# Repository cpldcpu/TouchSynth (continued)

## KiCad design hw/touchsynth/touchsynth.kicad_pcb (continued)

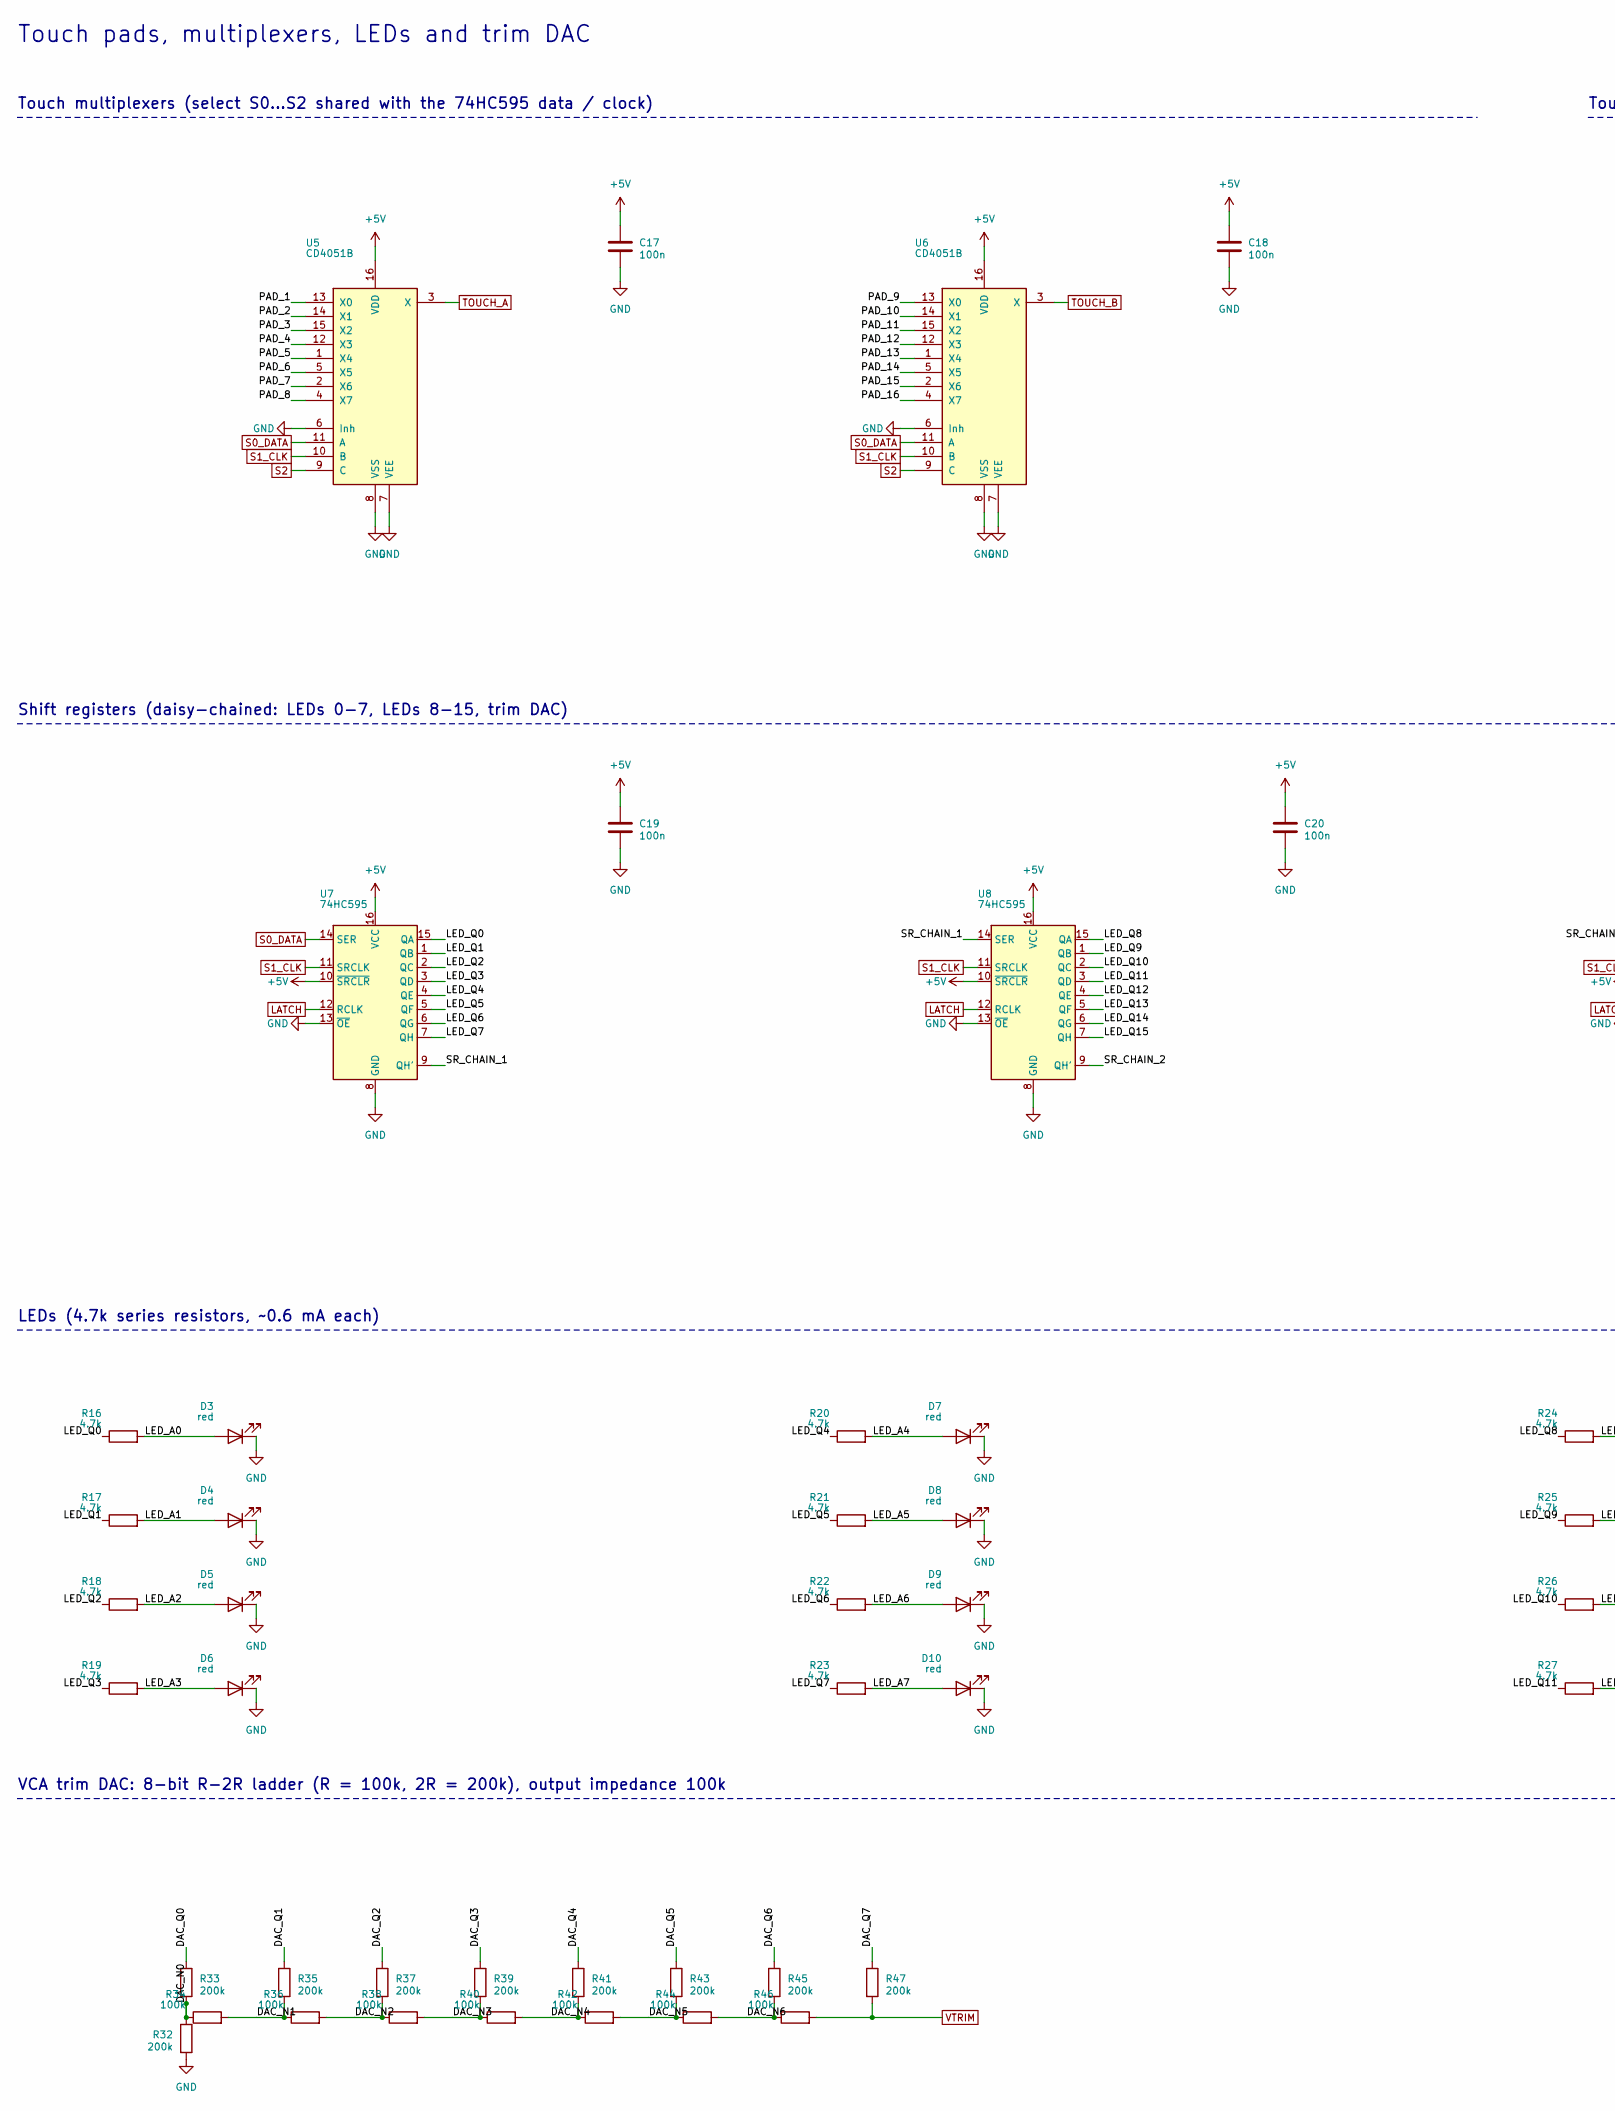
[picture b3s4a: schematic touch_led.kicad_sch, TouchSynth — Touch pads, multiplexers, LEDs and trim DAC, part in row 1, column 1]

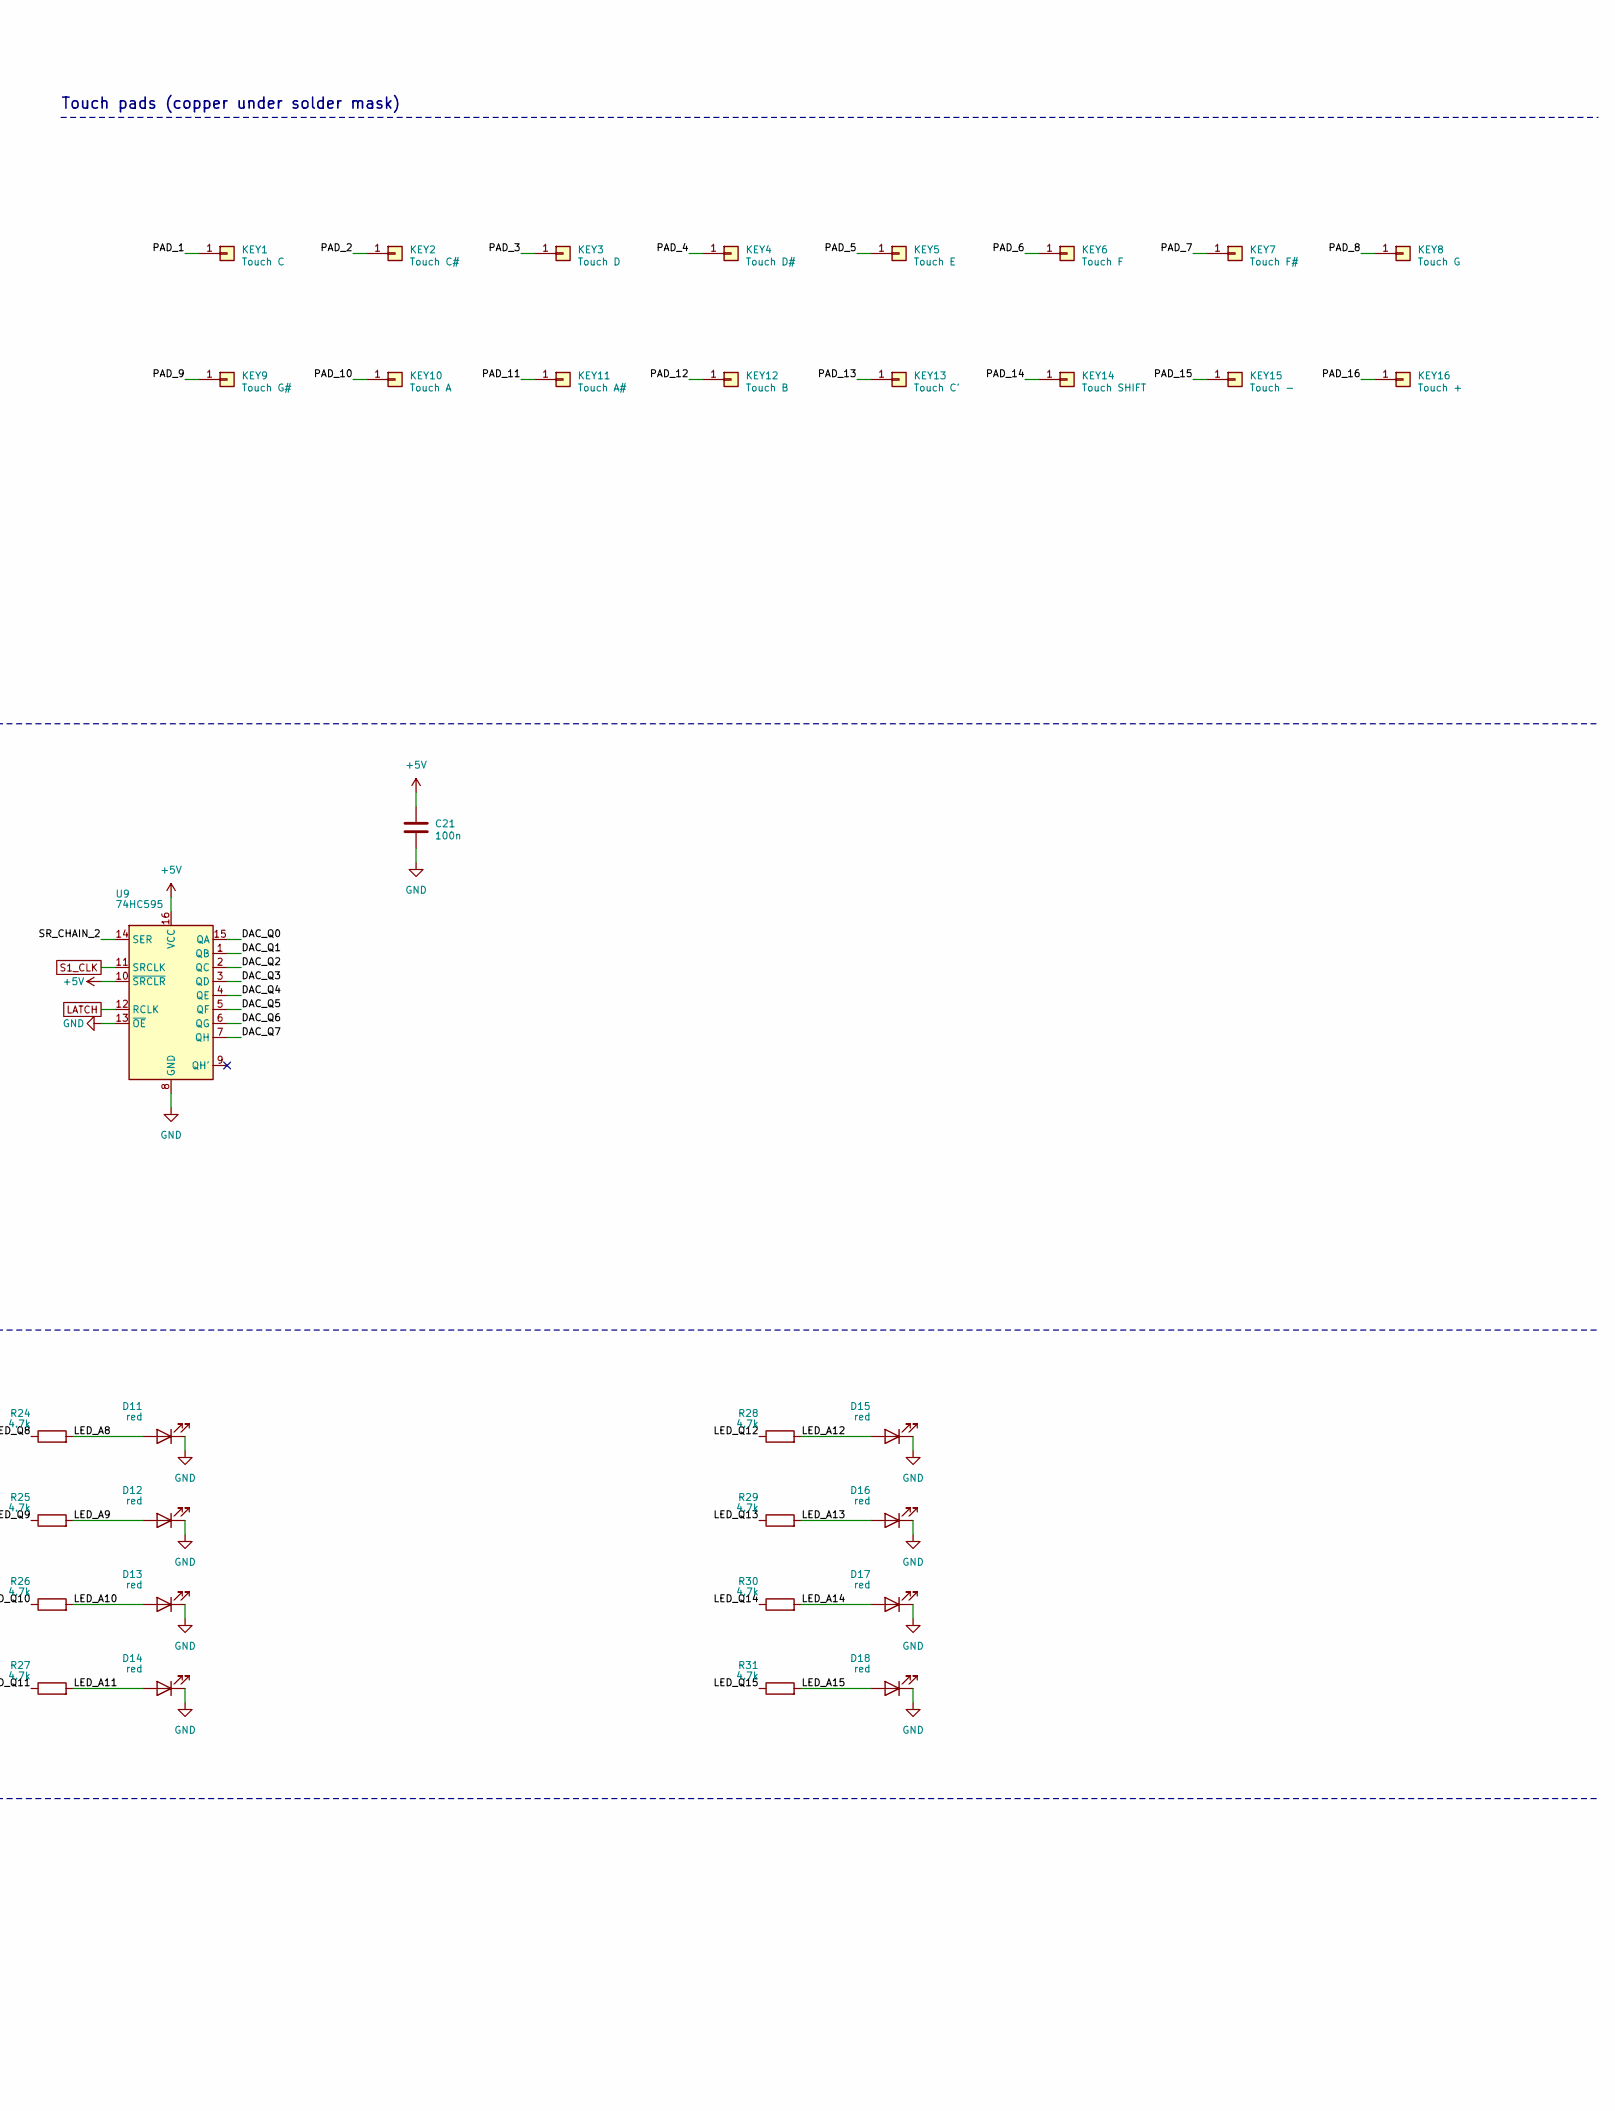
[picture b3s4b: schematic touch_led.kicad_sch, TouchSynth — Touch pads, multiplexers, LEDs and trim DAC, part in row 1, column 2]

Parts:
C17, C18, C19, C20, C21: 100n; C_0603_1608Metric; LCSC C14663
D3, D4, D5, D6, D7, D8, D9, D10, D11, D12, D13, D14, D15, D16, D17, D18: red; LED_0603_1608Metric; LCSC C2286
KEY1: Touch C; TouchPad_White
KEY2: Touch C#; TouchPad_Black
KEY3: Touch D; TouchPad_White
KEY4: Touch D#; TouchPad_Black
KEY5: Touch E; TouchPad_White
KEY6: Touch F; TouchPad_White
KEY7: Touch F#; TouchPad_Black
KEY8: Touch G; TouchPad_White
KEY9: Touch G#; TouchPad_Black
KEY10: Touch A; TouchPad_White
KEY11: Touch A#; TouchPad_Black
KEY12: Touch B; TouchPad_White
KEY13: Touch C'; TouchPad_White
KEY14: Touch SHIFT; TouchPad_Func
KEY15: Touch -; TouchPad_Func
KEY16: Touch +; TouchPad_Func
R16, R17, R18, R19, R20, R21, R22, R23, R24, R25, R26, R27, R28, R29, R30, R31: 4.7k; R_0603_1608Metric; LCSC C23162
R32, R33, R35, R37, R39, R41, R43, R45, R47: 200k; R_0603_1608Metric; LCSC C25811
R34, R36, R38, R40, R42, R44, R46: 100k; R_0603_1608Metric; LCSC C25803
U5, U6: CD4051B; SOIC-16_3.9x9.9mm_P1.27mm; LCSC C21379
U7, U8, U9: 74HC595; SOIC-16_3.9x9.9mm_P1.27mm; LCSC C5947

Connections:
+5V: C17.1, C18.1, C19.1, C20.1, C21.1, U5.16 (VDD), U6.16 (VDD), U7.10 (~SRCLR), U7.16 (VCC), U8.10 (~SRCLR), U8.16 (VCC), U9.10 (~SRCLR), U9.16 (VCC); also elsewhere on the board
/touch_led/DAC_N0: R32.1, R33.2, R34.1
/touch_led/DAC_N1: R34.2, R35.2, R36.1
/touch_led/DAC_N2: R36.2, R37.2, R38.1
/touch_led/DAC_N3: R38.2, R39.2, R40.1
/touch_led/DAC_N4: R40.2, R41.2, R42.1
/touch_led/DAC_N5: R42.2, R43.2, R44.1
/touch_led/DAC_N6: R44.2, R45.2, R46.1
/touch_led/DAC_Q0: R33.1, U9.15 (QA)
/touch_led/DAC_Q1: R35.1, U9.1 (QB)
/touch_led/DAC_Q2: R37.1, U9.2 (QC)
/touch_led/DAC_Q3: R39.1, U9.3 (QD)
/touch_led/DAC_Q4: R41.1, U9.4 (QE)
/touch_led/DAC_Q5: R43.1, U9.5 (QF)
/touch_led/DAC_Q6: R45.1, U9.6 (QG)
/touch_led/DAC_Q7: R47.1, U9.7 (QH)
/touch_led/LED_A0: D3.2 (A), R16.2
/touch_led/LED_A1: D4.2 (A), R17.2
/touch_led/LED_A2: D5.2 (A), R18.2
/touch_led/LED_A3: D6.2 (A), R19.2
/touch_led/LED_A4: D7.2 (A), R20.2
/touch_led/LED_A5: D8.2 (A), R21.2
/touch_led/LED_A6: D9.2 (A), R22.2
/touch_led/LED_A7: D10.2 (A), R23.2
/touch_led/LED_A8: D11.2 (A), R24.2
/touch_led/LED_A9: D12.2 (A), R25.2
/touch_led/LED_A10: D13.2 (A), R26.2
/touch_led/LED_A11: D14.2 (A), R27.2
/touch_led/LED_A12: D15.2 (A), R28.2
/touch_led/LED_A13: D16.2 (A), R29.2
/touch_led/LED_A14: D17.2 (A), R30.2
/touch_led/LED_A15: D18.2 (A), R31.2
/touch_led/LED_Q0: R16.1, U7.15 (QA)
/touch_led/LED_Q1: R17.1, U7.1 (QB)
/touch_led/LED_Q2: R18.1, U7.2 (QC)
/touch_led/LED_Q3: R19.1, U7.3 (QD)
/touch_led/LED_Q4: R20.1, U7.4 (QE)
/touch_led/LED_Q5: R21.1, U7.5 (QF)
/touch_led/LED_Q6: R22.1, U7.6 (QG)
/touch_led/LED_Q7: R23.1, U7.7 (QH)
/touch_led/LED_Q8: R24.1, U8.15 (QA)
/touch_led/LED_Q9: R25.1, U8.1 (QB)
/touch_led/LED_Q10: R26.1, U8.2 (QC)
/touch_led/LED_Q11: R27.1, U8.3 (QD)
/touch_led/LED_Q12: R28.1, U8.4 (QE)
/touch_led/LED_Q13: R29.1, U8.5 (QF)
/touch_led/LED_Q14: R30.1, U8.6 (QG)
/touch_led/LED_Q15: R31.1, U8.7 (QH)
/touch_led/PAD_1: KEY1.1, U5.13 (X0)
/touch_led/PAD_2: KEY2.1, U5.14 (X1)
/touch_led/PAD_3: KEY3.1, U5.15 (X2)
/touch_led/PAD_4: KEY4.1, U5.12 (X3)
/touch_led/PAD_5: KEY5.1, U5.1 (X4)
/touch_led/PAD_6: KEY6.1, U5.5 (X5)
/touch_led/PAD_7: KEY7.1, U5.2 (X6)
/touch_led/PAD_8: KEY8.1, U5.4 (X7)
/touch_led/PAD_9: KEY9.1, U6.13 (X0)
/touch_led/PAD_10: KEY10.1, U6.14 (X1)
/touch_led/PAD_11: KEY11.1, U6.15 (X2)
/touch_led/PAD_12: KEY12.1, U6.12 (X3)
/touch_led/PAD_13: KEY13.1, U6.1 (X4)
/touch_led/PAD_14: KEY14.1, U6.5 (X5)
/touch_led/PAD_15: KEY15.1, U6.2 (X6)
/touch_led/PAD_16: KEY16.1, U6.4 (X7)
/touch_led/SR_CHAIN_1: U7.9 (QH'), U8.14 (SER)
/touch_led/SR_CHAIN_2: U8.9 (QH'), U9.14 (SER)
GND: C17.2, C18.2, C19.2, C20.2, C21.2, D3.1 (K), D4.1 (K), D5.1 (K), D6.1 (K), D7.1 (K), D8.1 (K), D9.1 (K), D10.1 (K), D11.1 (K), D12.1 (K), D13.1 (K), D14.1 (K), D15.1 (K), D16.1 (K), D17.1 (K), D18.1 (K), R32.2, U5.6 (Inh), U5.7 (VEE), U5.8 (VSS), U6.6 (Inh), U6.7 (VEE), U6.8 (VSS), U7.8 (GND), U7.13 (~OE), U8.8 (GND), U8.13 (~OE), U9.8 (GND), U9.13 (~OE); also elsewhere on the board
LATCH: U7.12 (RCLK), U8.12 (RCLK), U9.12 (RCLK); also elsewhere on the board
S0_DATA: U5.11 (A), U6.11 (A), U7.14 (SER); also elsewhere on the board
S1_CLK: U5.10 (B), U6.10 (B), U7.11 (SRCLK), U8.11 (SRCLK), U9.11 (SRCLK); also elsewhere on the board
S2: U5.9 (C), U6.9 (C); also elsewhere on the board
TOUCH_A: U5.3 (X); also elsewhere on the board
TOUCH_B: U6.3 (X); also elsewhere on the board
VTRIM: R46.2, R47.2; also elsewhere on the board

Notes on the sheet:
Touch pads, multiplexers, LEDs and trim DAC
Touch multiplexers (select S0...S2 shared with the 74HC595 data / clock)
Touch pads (copper under solder mask)
Shift registers (daisy-chained: LEDs 0-7, LEDs 8-15, trim DAC)
LEDs (4.7k series resistors, ~0.6 mA each)
VCA trim DAC: 8-bit R-2R ladder (R = 100k, 2R = 200k), output impedance 100k

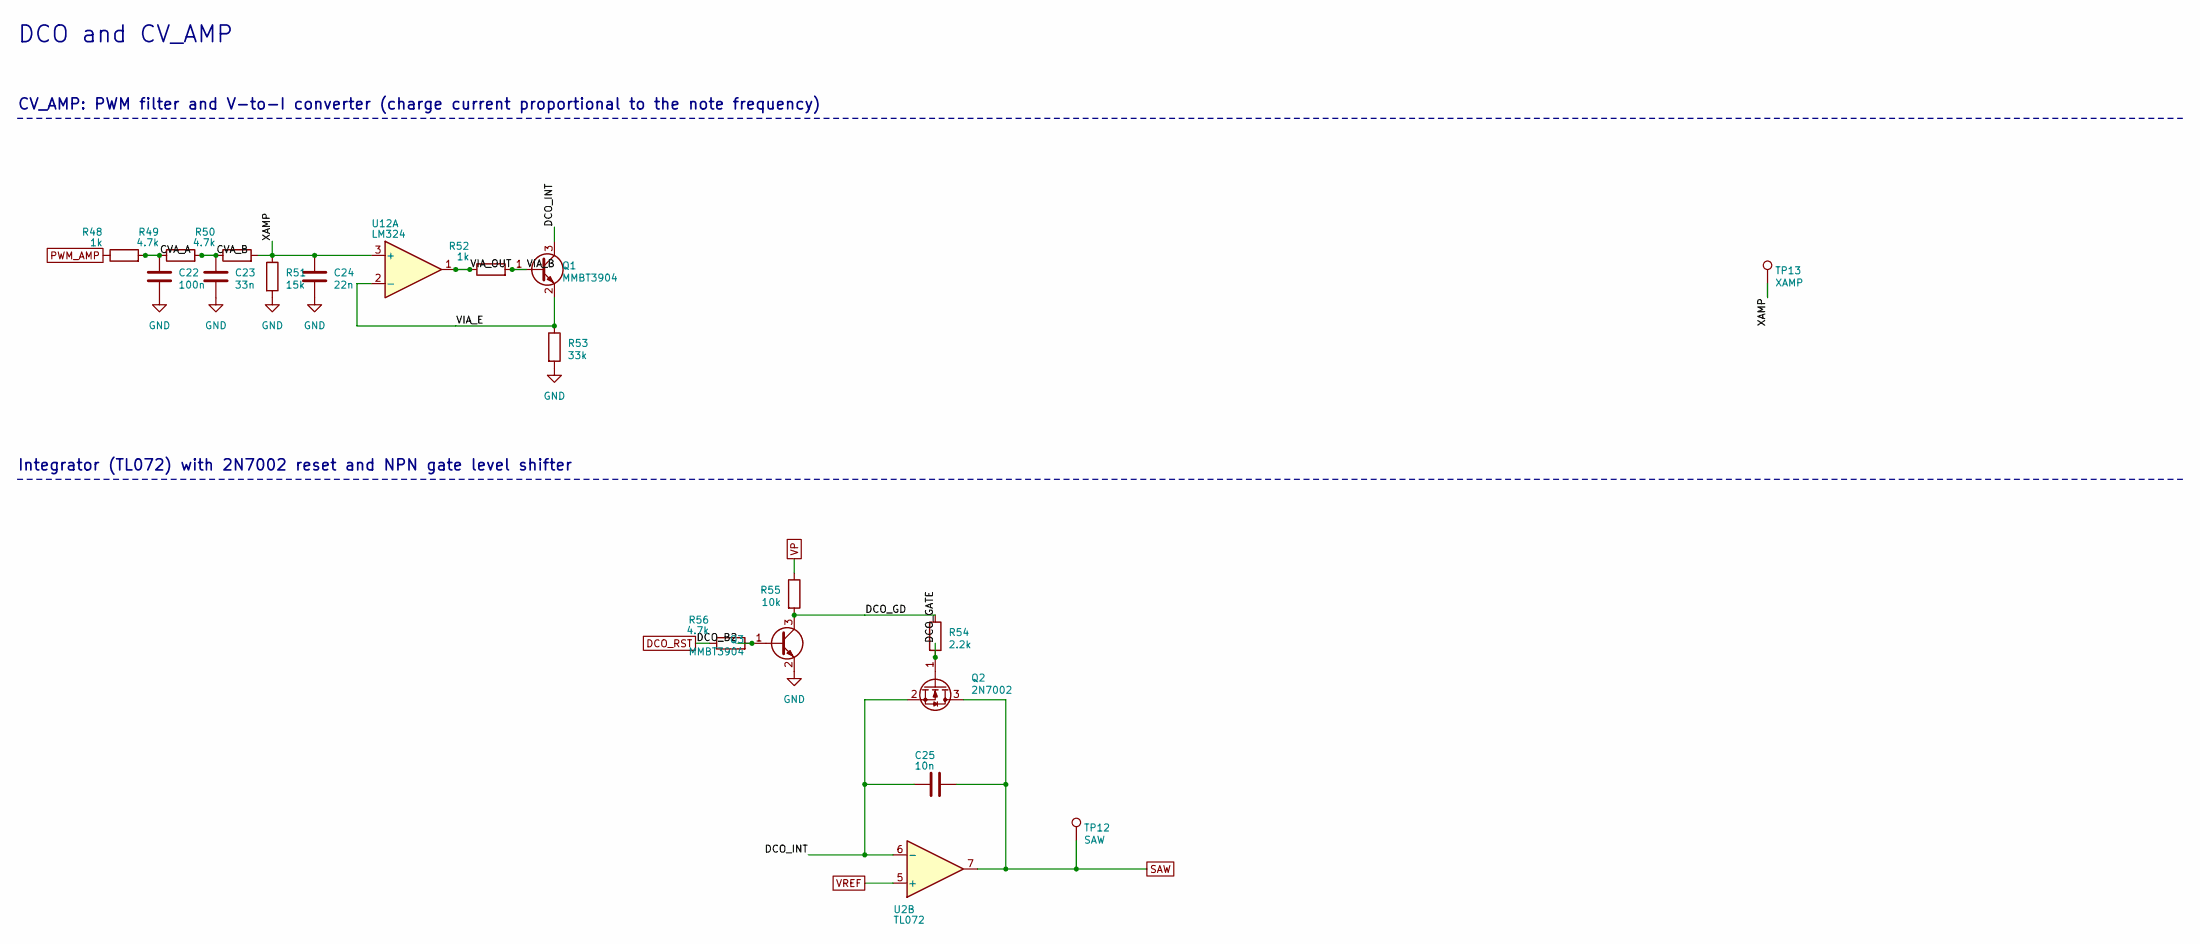
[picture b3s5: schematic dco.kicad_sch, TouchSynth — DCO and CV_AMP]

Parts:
C22: 100n; C_0603_1608Metric; LCSC C14663
C23: 33n; C_0603_1608Metric; LCSC C21117
C24: 22n; C_0603_1608Metric; LCSC C21122
C25: 10n; C_0603_1608Metric; LCSC C57112
Q1, Q3: MMBT3904; SOT-23; LCSC C20526
Q2: 2N7002; SOT-23; LCSC C8545
R48, R52: 1k; R_0603_1608Metric; LCSC C21190
R49, R50, R56: 4.7k; R_0603_1608Metric; LCSC C23162
R51: 15k; R_0603_1608Metric; LCSC C22809
R53: 33k; R_0603_1608Metric; LCSC C4216
R54: 2.2k; R_0603_1608Metric; LCSC C4190
R55: 10k; R_0603_1608Metric; LCSC C25804
TP12: SAW; TestPoint_Pad_D1.0mm
TP13: XAMP; TestPoint_Pad_D1.0mm
U2: TL072; SOIC-8_3.9x4.9mm_P1.27mm; LCSC C6961
U12: LM324; SOIC-14_3.9x8.7mm_P1.27mm; LCSC C71035

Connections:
/dco/CVA_A: C22.1, R48.2, R49.1
/dco/CVA_B: C23.1, R49.2, R50.1
/dco/DCO_B2: Q3.1 (B), R56.2
/dco/DCO_GATE: Q2.1 (G), R54.2
/dco/DCO_GD: Q3.3 (C), R54.1, R55.2
/dco/DCO_INT: C25.2, Q1.3 (C), Q2.2 (S), U2.6 (-)
/dco/VIA_B: Q1.1 (B), R52.2
/dco/VIA_E: Q1.2 (E), R53.1, U12.2 (-)
/dco/VIA_OUT: R52.1, U12.1
/dco/XAMP: C24.1, R50.2, R51.1, TP13.1, U12.3 (+)
DCO_RST: R56.1; also elsewhere on the board
GND: C22.2, C23.2, C24.2, Q3.2 (E), R51.2, R53.2; also elsewhere on the board
PWM_AMP: R48.1; also elsewhere on the board
SAW: C25.1, Q2.3 (D), TP12.1, U2.7; also elsewhere on the board
VP: R55.1; also elsewhere on the board
VREF: U2.5 (+); also elsewhere on the board

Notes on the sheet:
DCO and CV_AMP
CV_AMP: PWM filter and V-to-I converter (charge current proportional to the note frequency)
Integrator (TL072) with 2N7002 reset and NPN gate level shifter

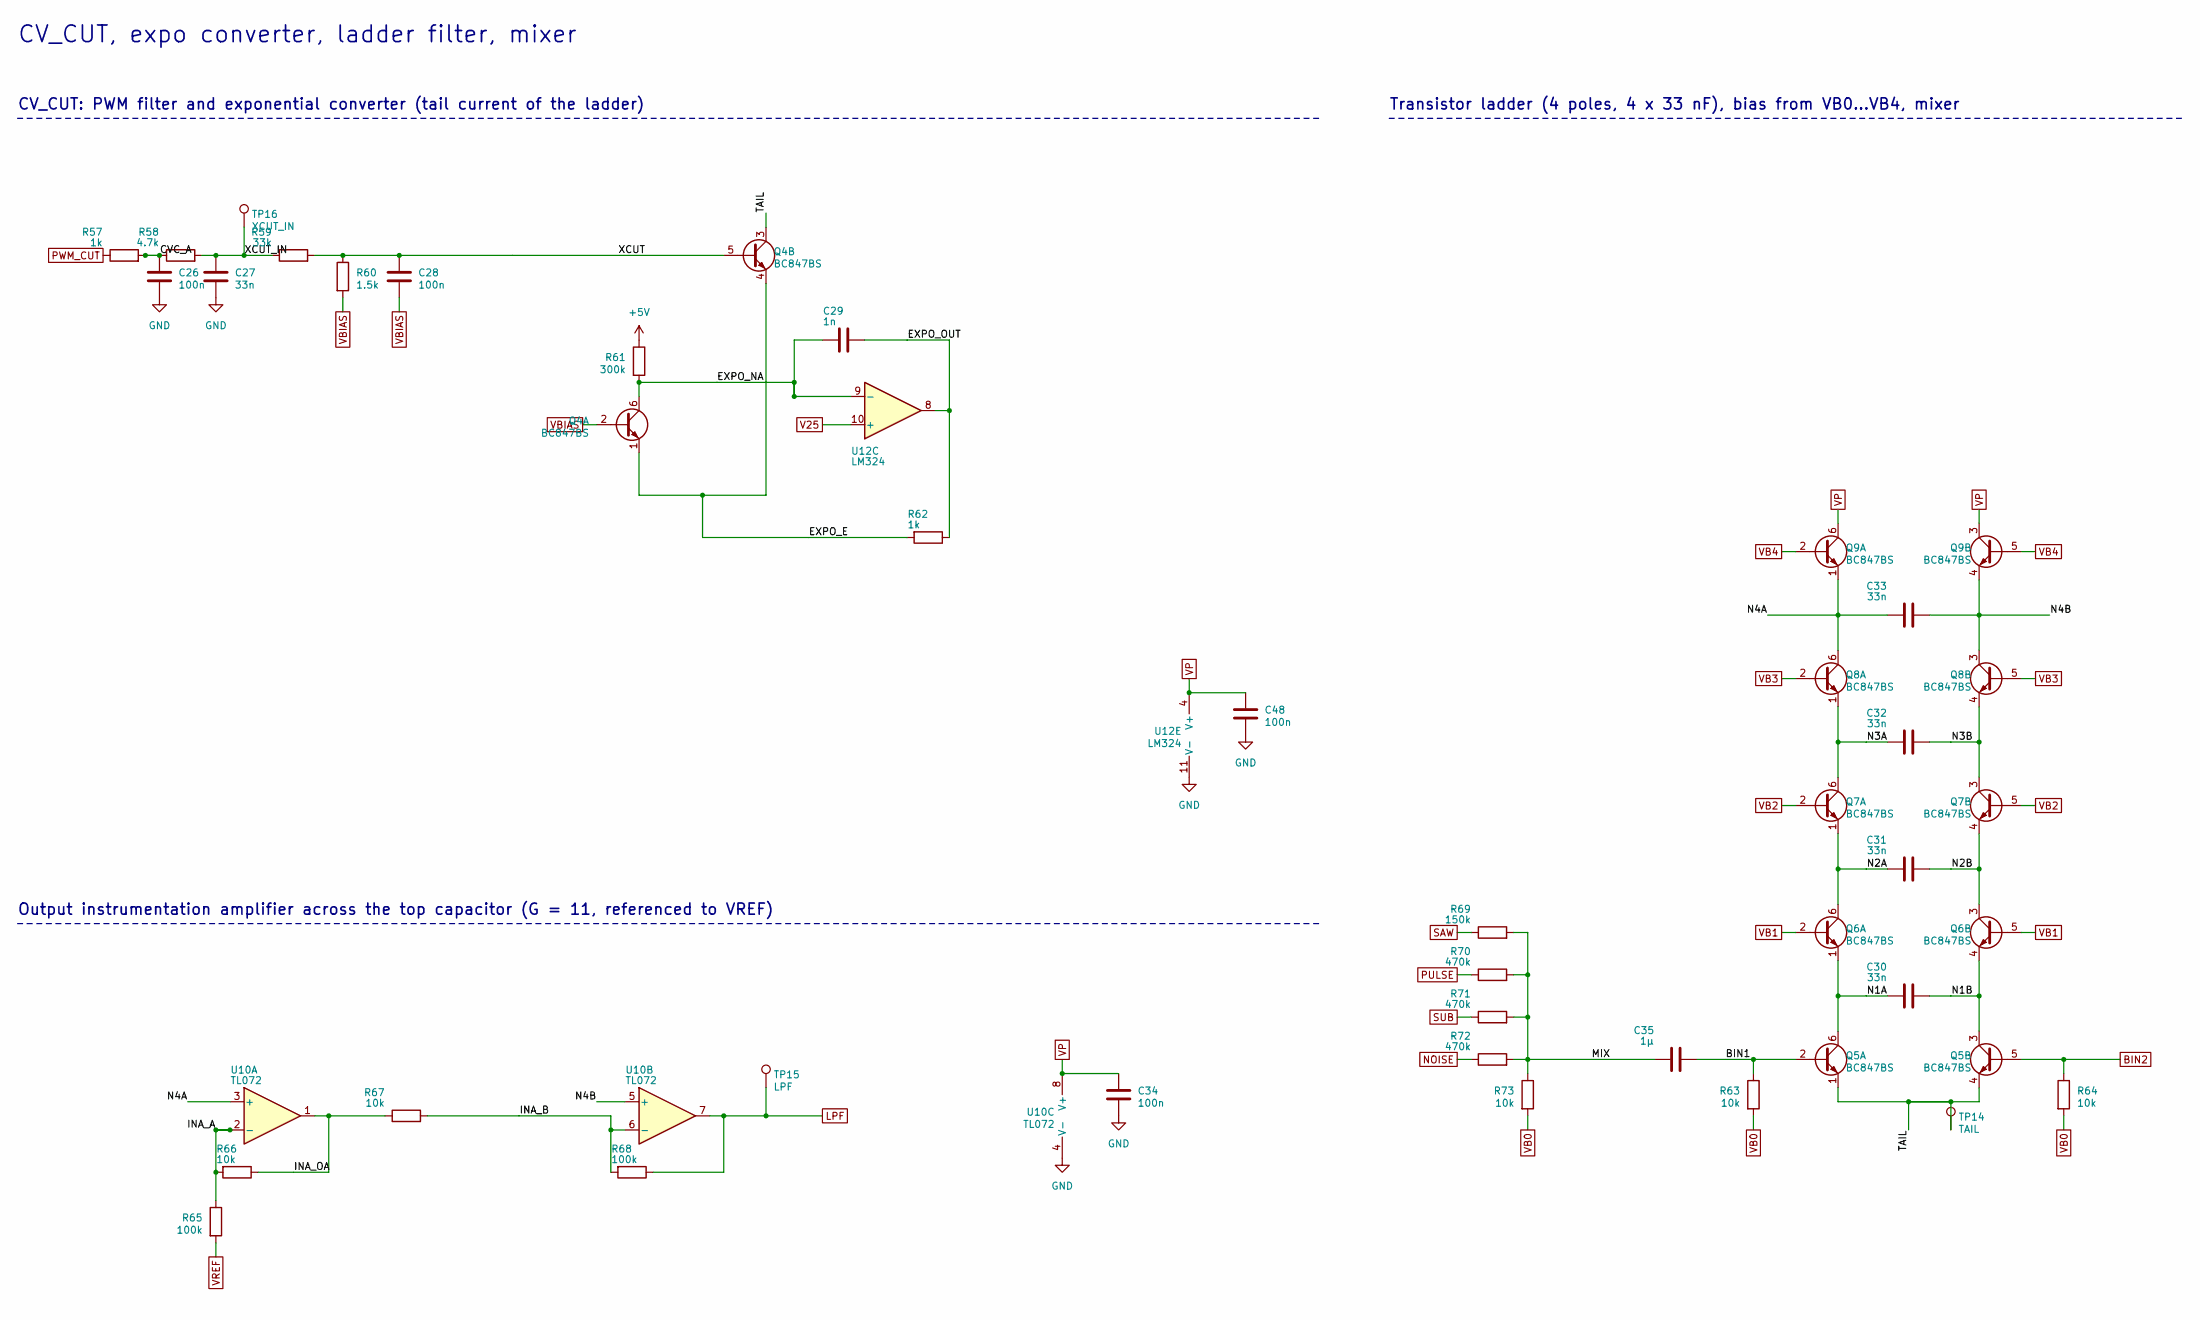
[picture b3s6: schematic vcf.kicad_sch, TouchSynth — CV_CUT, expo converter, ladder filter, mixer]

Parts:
C26, C28, C34, C48: 100n; C_0603_1608Metric; LCSC C14663
C27, C30, C31, C32, C33: 33n; C_0603_1608Metric; LCSC C21117
C29: 1n; C_0603_1608Metric; LCSC C1588
C35: 1µ; C_0603_1608Metric; LCSC C15849
Q4, Q5, Q6, Q7, Q8, Q9: BC847BS; SOT-363_SC-70-6; LCSC C41375126
R57, R62: 1k; R_0603_1608Metric; LCSC C21190
R58: 4.7k; R_0603_1608Metric; LCSC C23162
R59: 33k; R_0603_1608Metric; LCSC C4216
R60: 1.5k; R_0603_1608Metric; LCSC C22843
R61: 300k; R_0603_1608Metric; LCSC C23024
R63, R64, R66, R67, R73: 10k; R_0603_1608Metric; LCSC C25804
R65, R68: 100k; R_0603_1608Metric; LCSC C25803
R69: 150k; R_0603_1608Metric; LCSC C22807
R70, R71, R72: 470k; R_0603_1608Metric; LCSC C23178
TP14: TAIL; TestPoint_Pad_D1.0mm
TP15: LPF; TestPoint_Pad_D1.0mm
TP16: XCUT_IN; TestPoint_Pad_D1.0mm
U10: TL072; SOIC-8_3.9x4.9mm_P1.27mm; LCSC C6961
U12: LM324; SOIC-14_3.9x8.7mm_P1.27mm; LCSC C71035

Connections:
+5V: R61.1; also elsewhere on the board
/vcf/BIN1: C35.2, Q5.2 (B1), R63.1
/vcf/CVC_A: C26.1, R57.2, R58.1
/vcf/EXPO_E: Q4.1 (E1), Q4.4 (E2), R62.2
/vcf/EXPO_NA: C29.2, Q4.6 (C1), R61.2, U12.9 (-)
/vcf/EXPO_OUT: C29.1, R62.1, U12.8
/vcf/INA_A: R65.1, R66.2, U10.2 (-)
/vcf/INA_B: R67.2, R68.2, U10.6 (-)
/vcf/INA_OA: R66.1, R67.1, U10.1
/vcf/MIX: C35.1, R69.2, R70.2, R71.2, R72.2, R73.1
/vcf/N1A: C30.1, Q5.6 (C1), Q6.1 (E1)
/vcf/N1B: C30.2, Q5.3 (C2), Q6.4 (E2)
/vcf/N2A: C31.1, Q6.6 (C1), Q7.1 (E1)
/vcf/N2B: C31.2, Q6.3 (C2), Q7.4 (E2)
/vcf/N3A: C32.1, Q7.6 (C1), Q8.1 (E1)
/vcf/N3B: C32.2, Q7.3 (C2), Q8.4 (E2)
/vcf/N4A: C33.1, Q8.6 (C1), Q9.1 (E1), U10.3 (+)
/vcf/N4B: C33.2, Q8.3 (C2), Q9.4 (E2), U10.5 (+)
/vcf/TAIL: Q4.3 (C2), Q5.1 (E1), Q5.4 (E2), TP14.1
/vcf/XCUT: C28.1, Q4.5 (B2), R59.2, R60.1
/vcf/XCUT_IN: C27.1, R58.2, R59.1, TP16.1
BIN2: Q5.5 (B2), R64.1; also elsewhere on the board
GND: C26.2, C27.2, C34.2, C48.2, U10.4 (V-), U12.11 (V-); also elsewhere on the board
LPF: R68.1, TP15.1, U10.7; also elsewhere on the board
NOISE: R72.1; also elsewhere on the board
PULSE: R70.1; also elsewhere on the board
PWM_CUT: R57.1; also elsewhere on the board
SAW: R69.1; also elsewhere on the board
SUB: R71.1; also elsewhere on the board
V25: U12.10 (+); also elsewhere on the board
VB0: R63.2, R64.2, R73.2; also elsewhere on the board
VB1: Q6.2 (B1), Q6.5 (B2); also elsewhere on the board
VB2: Q7.2 (B1), Q7.5 (B2); also elsewhere on the board
VB3: Q8.2 (B1), Q8.5 (B2); also elsewhere on the board
VB4: Q9.2 (B1), Q9.5 (B2); also elsewhere on the board
VBIAS: C28.2, Q4.2 (B1), R60.2; also elsewhere on the board
VP: C34.1, C48.1, Q9.3 (C2), Q9.6 (C1), U10.8 (V+), U12.4 (V+); also elsewhere on the board
VREF: R65.2; also elsewhere on the board

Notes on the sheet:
CV_CUT, expo converter, ladder filter, mixer
CV_CUT: PWM filter and exponential converter (tail current of the ladder)
Transistor ladder (4 poles, 4 x 33 nF), bias from VB0...VB4, mixer
Output instrumentation amplifier across the top capacitor (G = 11, referenced to VREF)

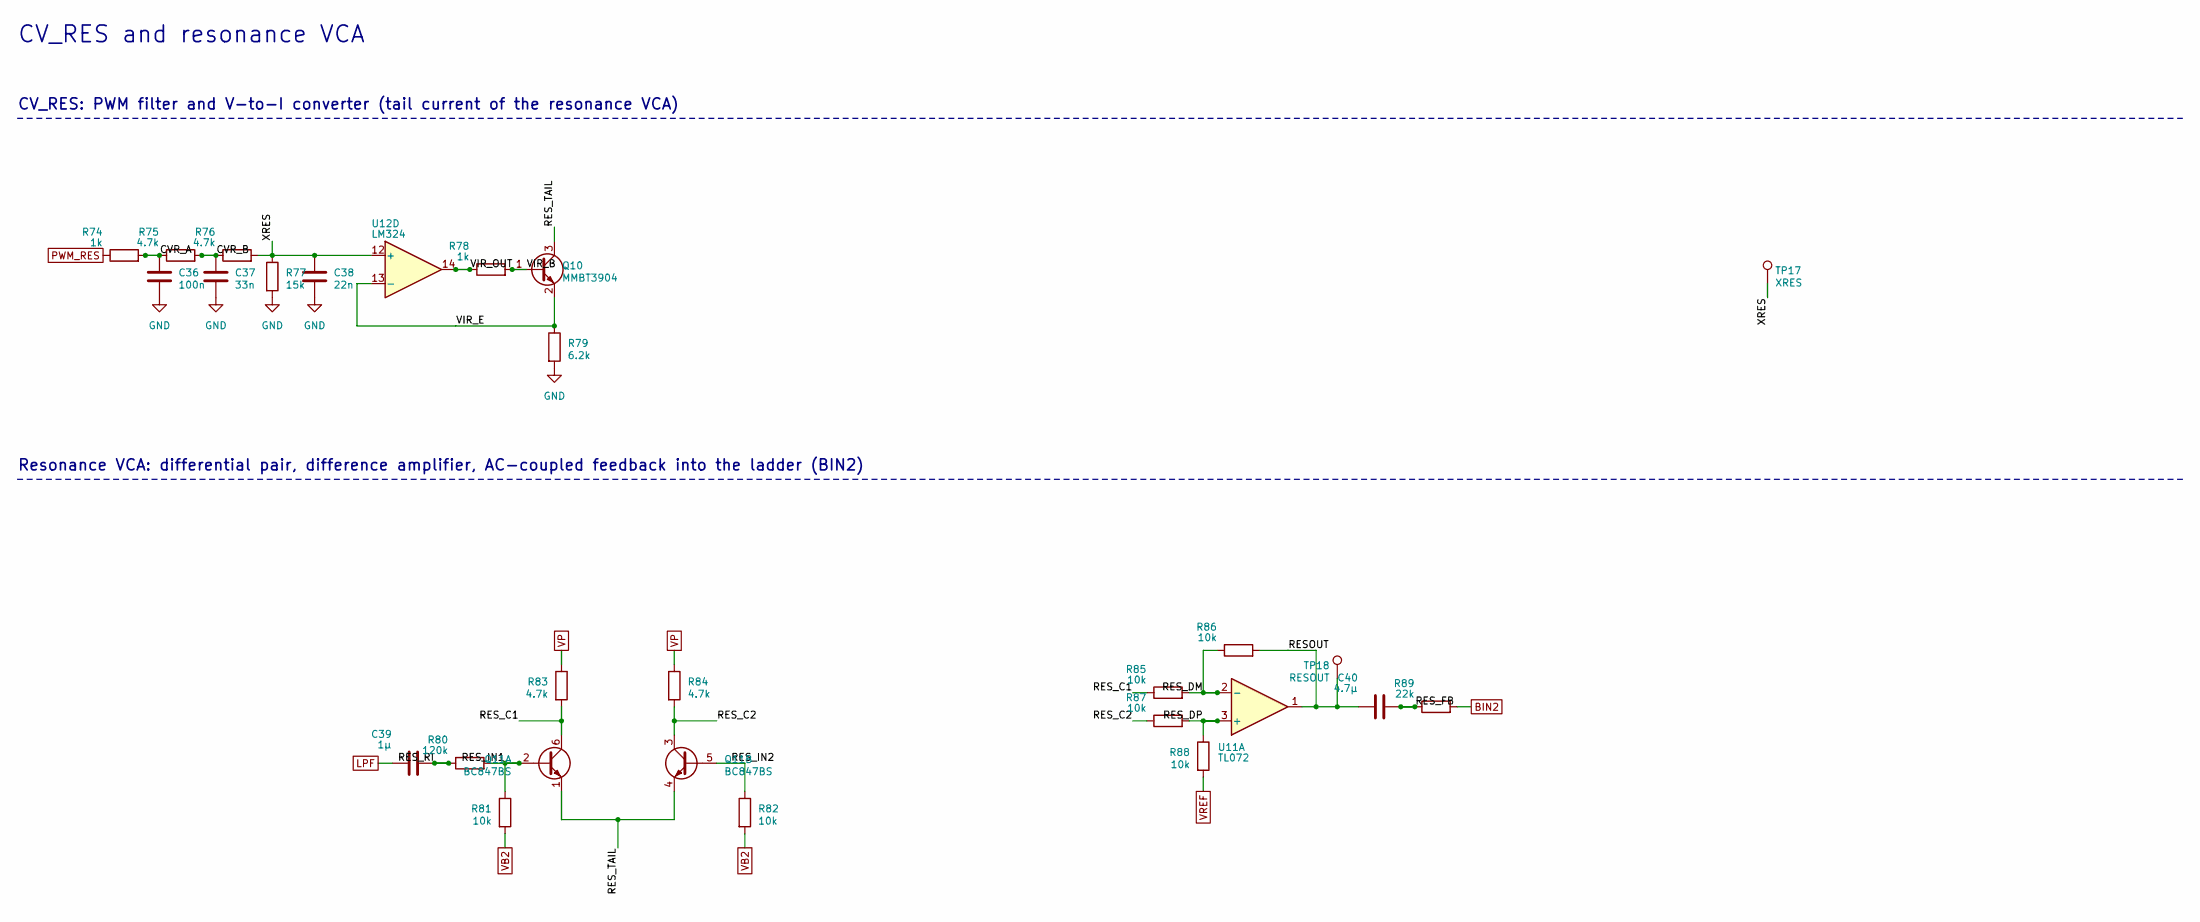
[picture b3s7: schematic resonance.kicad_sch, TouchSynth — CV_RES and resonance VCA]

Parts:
C36: 100n; C_0603_1608Metric; LCSC C14663
C37: 33n; C_0603_1608Metric; LCSC C21117
C38: 22n; C_0603_1608Metric; LCSC C21122
C39: 1µ; C_0603_1608Metric; LCSC C15849
C40: 4.7µ; C_0603_1608Metric; LCSC C19666
Q10: MMBT3904; SOT-23; LCSC C20526
Q11: BC847BS; SOT-363_SC-70-6; LCSC C41375126
R74, R78: 1k; R_0603_1608Metric; LCSC C21190
R75, R76, R83, R84: 4.7k; R_0603_1608Metric; LCSC C23162
R77: 15k; R_0603_1608Metric; LCSC C22809
R79: 6.2k; R_0603_1608Metric; LCSC C4260
R80: 120k; R_0603_1608Metric; LCSC C25808
R81, R82, R85, R86, R87, R88: 10k; R_0603_1608Metric; LCSC C25804
R89: 22k; R_0603_1608Metric; LCSC C31850
TP17: XRES; TestPoint_Pad_D1.0mm
TP18: RESOUT; TestPoint_Pad_D1.0mm
U11: TL072; SOIC-8_3.9x4.9mm_P1.27mm; LCSC C6961
U12: LM324; SOIC-14_3.9x8.7mm_P1.27mm; LCSC C71035

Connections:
/resonance/CVR_A: C36.1, R74.2, R75.1
/resonance/CVR_B: C37.1, R75.2, R76.1
/resonance/RESOUT: C40.1, R86.2, TP18.1, U11.1
/resonance/RES_C1: Q11.6 (C1), R83.2, R85.1
/resonance/RES_C2: Q11.3 (C2), R84.2, R87.1
/resonance/RES_DM: R85.2, R86.1, U11.2 (-)
/resonance/RES_DP: R87.2, R88.1, U11.3 (+)
/resonance/RES_FB: C40.2, R89.1
/resonance/RES_IN1: Q11.2 (B1), R80.2, R81.1
/resonance/RES_IN2: Q11.5 (B2), R82.1
/resonance/RES_RI: C39.2, R80.1
/resonance/RES_TAIL: Q10.3 (C), Q11.1 (E1), Q11.4 (E2)
/resonance/VIR_B: Q10.1 (B), R78.2
/resonance/VIR_E: Q10.2 (E), R79.1, U12.13 (-)
/resonance/VIR_OUT: R78.1, U12.14
/resonance/XRES: C38.1, R76.2, R77.1, TP17.1, U12.12 (+)
BIN2: R89.2; also elsewhere on the board
GND: C36.2, C37.2, C38.2, R77.2, R79.2; also elsewhere on the board
LPF: C39.1; also elsewhere on the board
PWM_RES: R74.1; also elsewhere on the board
VB2: R81.2, R82.2; also elsewhere on the board
VP: R83.1, R84.1; also elsewhere on the board
VREF: R88.2; also elsewhere on the board

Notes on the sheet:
CV_RES and resonance VCA
CV_RES: PWM filter and V-to-I converter (tail current of the resonance VCA)
Resonance VCA: differential pair, difference amplifier, AC-coupled feedback into the ladder (BIN2)
